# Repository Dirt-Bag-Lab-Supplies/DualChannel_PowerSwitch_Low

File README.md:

# DualChannel_PowerSwitch_Low
Dual Channel Low side power switch

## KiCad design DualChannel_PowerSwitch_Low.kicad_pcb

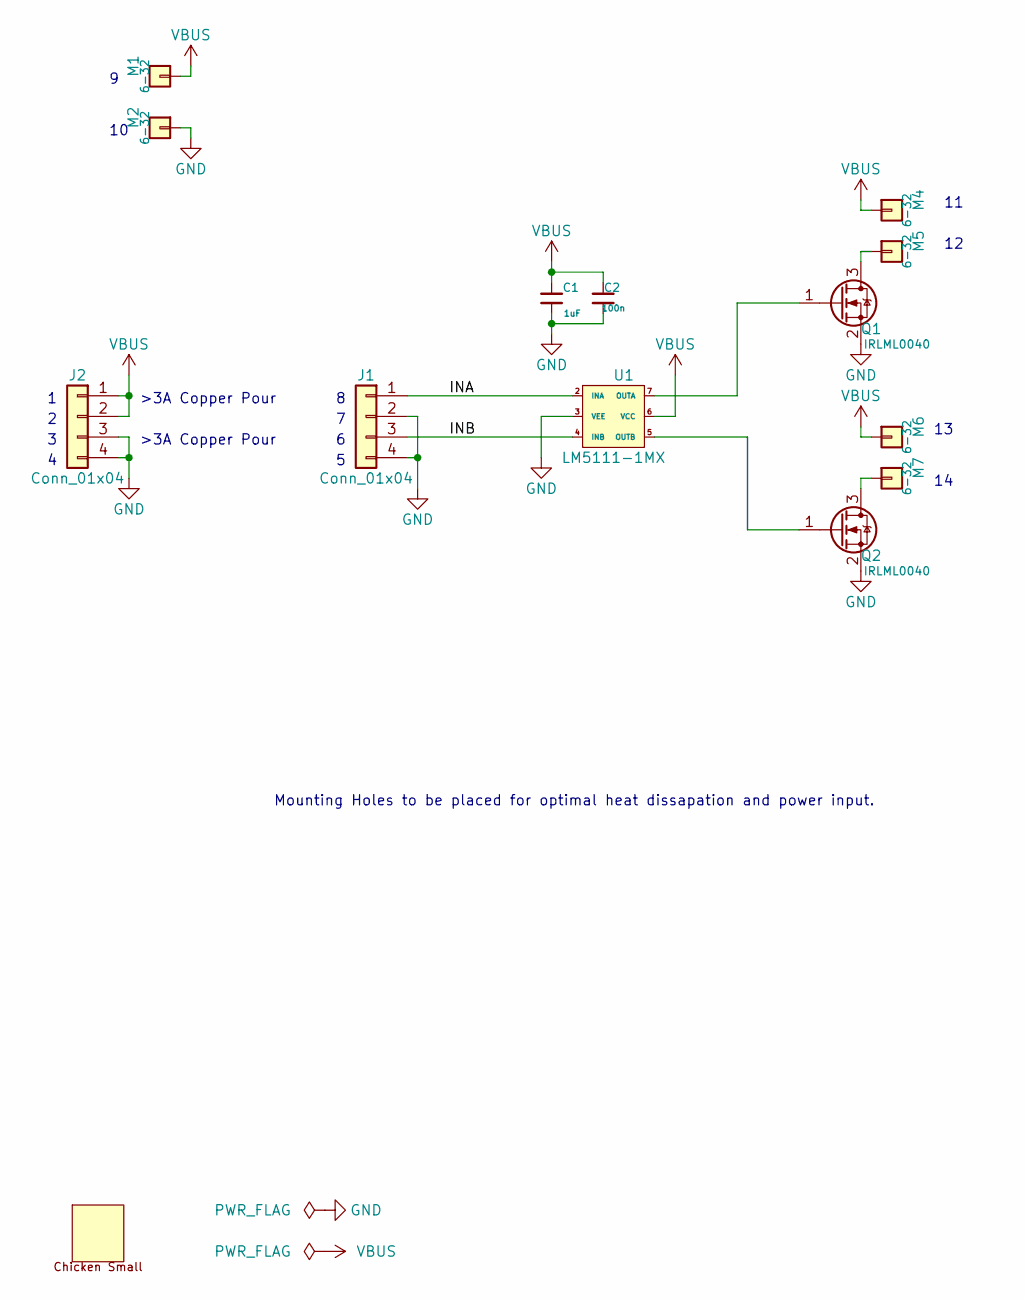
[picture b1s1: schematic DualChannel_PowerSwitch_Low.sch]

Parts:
C1: SMD-CAP-1UF-0402; C_0402_1005Metric; mfg_pn GRM155R61E105KA12D
C2: MURATA_GCM155R71C104KA55J; C_0402; mfg_pn GCM155R71C104KA55J
J1, J2: Conn_01x04; Pin_Header_Straight_1x04_Pitch2.54mm
LOGO1: DBLS_Chicken_Small; Rooster_4mmx4mm
M1, M2, M4, M5, M6, M7: SCREW_6-32_POWER
Q1, Q2: INFINEON_IRLML0040TRPBF; SOT-23; mfg_pn IRLML0040TRPBF
U1: TI_LM5111-1MX_NOPB; SOIC-8_3.9x4.9mm_Pitch1.27mm; mfg_pn LM5111-1MX/NOPB

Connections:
/INA: J1.1, U1.2 (INA)
/INB: J1.3, U1.4 (INB)
GND: C1.2, C2.2, J1.2, J1.4, J2.3, J2.4, M2.1, Q1.2 (S), Q2.2 (S), U1.3 (VEE)
unnamed: M5.1, Q1.3 (D)
unnamed: M7.1, Q2.3 (D)
unnamed: Q1.1 (G), U1.7 (OUTA)
unnamed: Q2.1 (G), U1.5 (OUTB)
VBUS: C1.1, C2.1, J2.1, J2.2, M1.1, M4.1, M6.1, U1.6 (VCC)

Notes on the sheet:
>3A Copper Pour
Mounting Holes to be placed for optimal heat dissapation and power input.

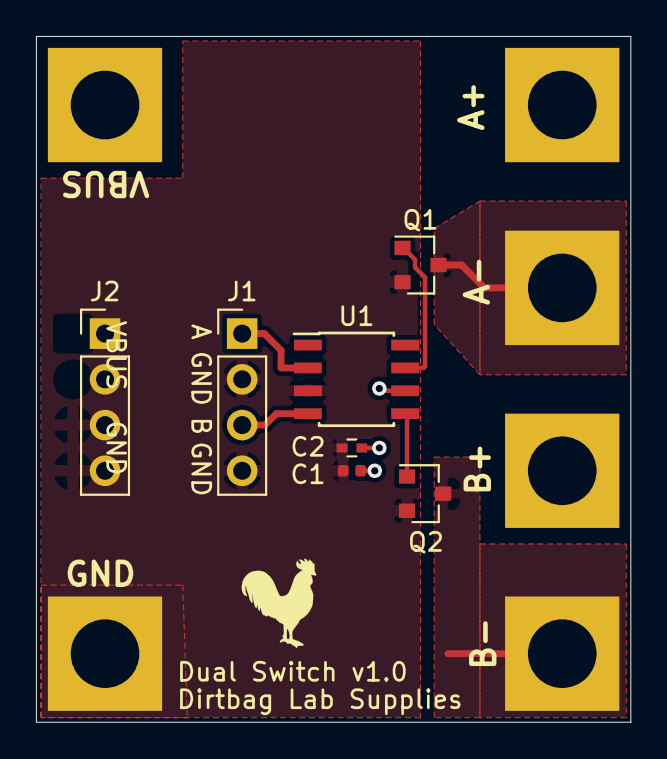
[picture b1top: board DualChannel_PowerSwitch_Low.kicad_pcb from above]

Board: 2 copper layers, 33.0 x 38.1 mm, 14 parts (0 on the bottom side), 8 nets.

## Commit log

2021-10-15 First commit. First draft layout with LM5111-1
2021-10-15 Adjusted header position slightly
